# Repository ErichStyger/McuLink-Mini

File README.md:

# McuLink-Mini
Version of the NXP MCU-Link CMSIS-DAP Debug Probe with KiCad.
Many thanks to *Dario Scheuber* and his work to make this project possible!

## Background
This is the work of Dario Scheuber who created this debug probe as student at the Lucerne University of Applied Sciences and Arts at [IET](https://www.hslu.ch/en/lucerne-school-of-engineering-architecture/about-us/organization/institute/engineering-and-technology/elektrotechnik/). The project was done under the guidance of Prof. Erich Styger.

See blog article on https://mcuoneclipse.com/2024/02/06/versatile-oshw-mini-mcu-link-debug-probe-external-on-board-or-embedded/ for additional details.

## Features
This is an open hardware version of the NXP MCU-Link CMSIS-DAP debug probe, with following features and differences to the original MCU-Link:
- Open hardware design with KiCad
- Firmware compatibility with MCU-Link (LinkServer, CMSIS-DAP, ARM DAPLink)
- Dual-Layer design for lower costs
- USB-C connector instead of  Micro-USB
- USB-C connector usable to debug the LPC55S69
- 30% smaller than the original MCU-Link
- Firmware/boot push button instead of jumper
- Micro connector for UART connection instead of pin header
- Supports only 3.3V targets (no level shifters)
- Standalone version as external debug probe
- On-Board version: Solder external debug probe on your custom board (castellated pins)
- Embedded version: copy-paste into your custom board KiCad design
- BOM with assembly costs: ~$12/piece for 100 units

## Folders
- enclosure: 3D printed enclosure
- hardware: KiCad and hardware related files

## Links
- Article: https://mcuoneclipse.com/2024/02/06/versatile-oshw-mini-mcu-link-debug-probe-external-on-board-or-embedded/
- NXP MCU-Link: https://www.nxp.com/design/design-center/software/development-software/mcuxpresso-software-and-tools-/mcu-link-debug-probe:MCU-LINK
- KiCad: https://www.kicad.org/

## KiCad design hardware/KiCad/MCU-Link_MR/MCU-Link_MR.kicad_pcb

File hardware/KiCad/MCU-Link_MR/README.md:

# MCU-Link

Project for the NXP MCU-Link Debug Probe with KiCAD, as a debug drone for mobile robotics platforms.

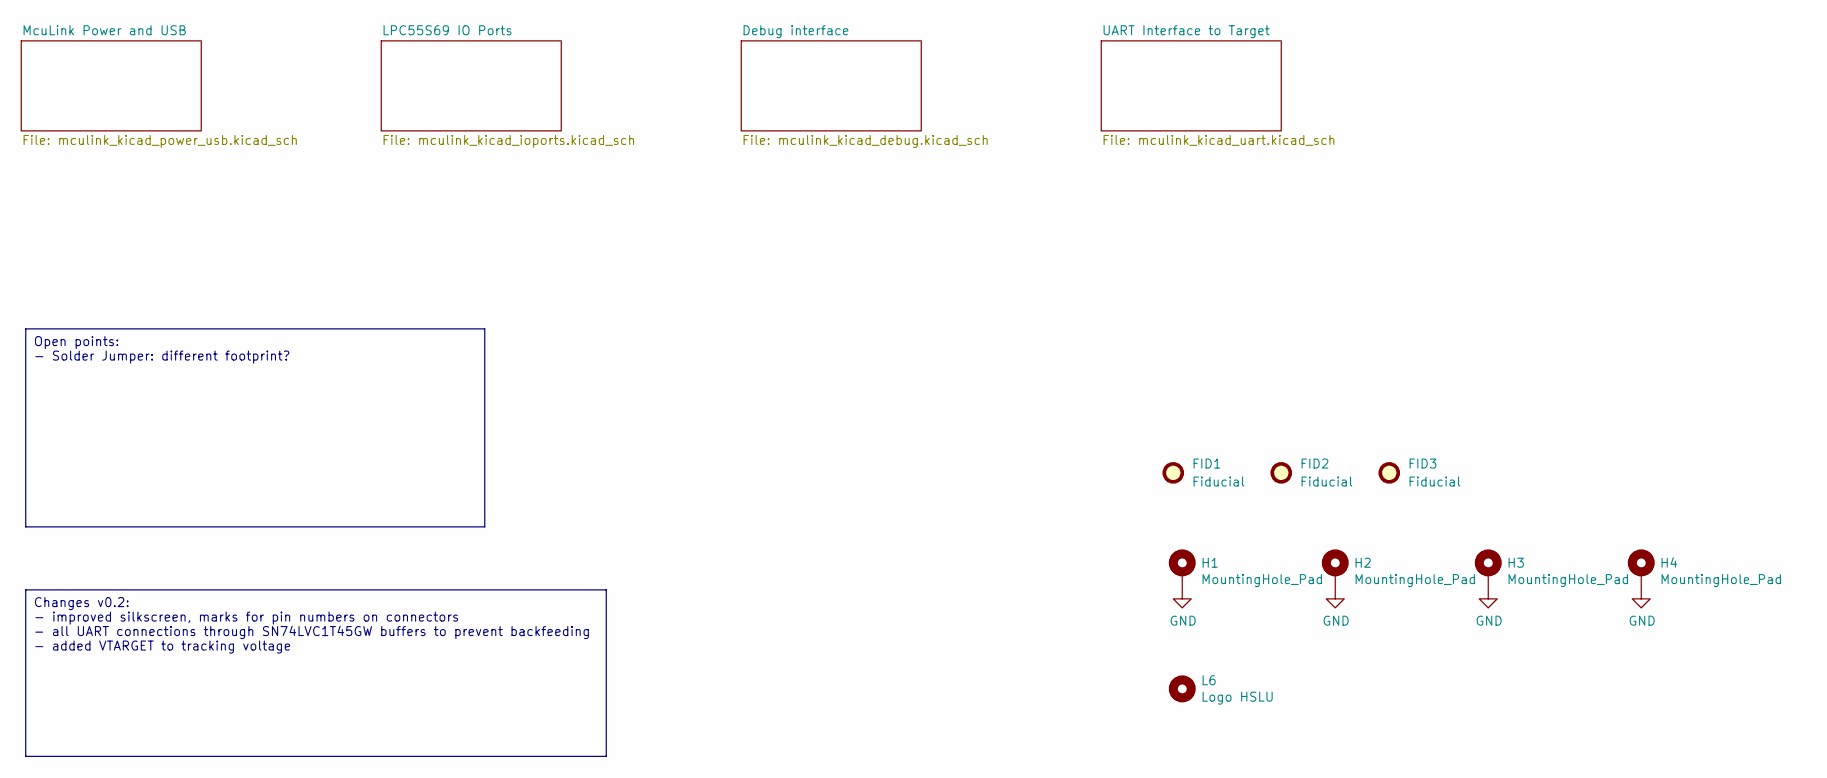
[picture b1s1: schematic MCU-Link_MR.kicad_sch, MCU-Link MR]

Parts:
FID1, FID2, FID3: Fiducial; Fiducial_1mm_Dia_2.54mm_Outer_CopperTop
H1, H2, H3, H4: MountingHole_Pad; MountingHole_2.7mm_M2.5_DIN965_Pad
L6: Logo HSLU; Hochschule_Luzern_New

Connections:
GND: H1.1, H2.1, H3.1, H4.1; also elsewhere on the board

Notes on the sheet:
Open points: - Solder Jumper: different footprint?
Changes v0.2: - improved silkscreen, marks for pin numbers on connectors - all UART connections through SN74LVC1T45GW buffers to prevent backfeeding - added VTARGET to tracking voltage

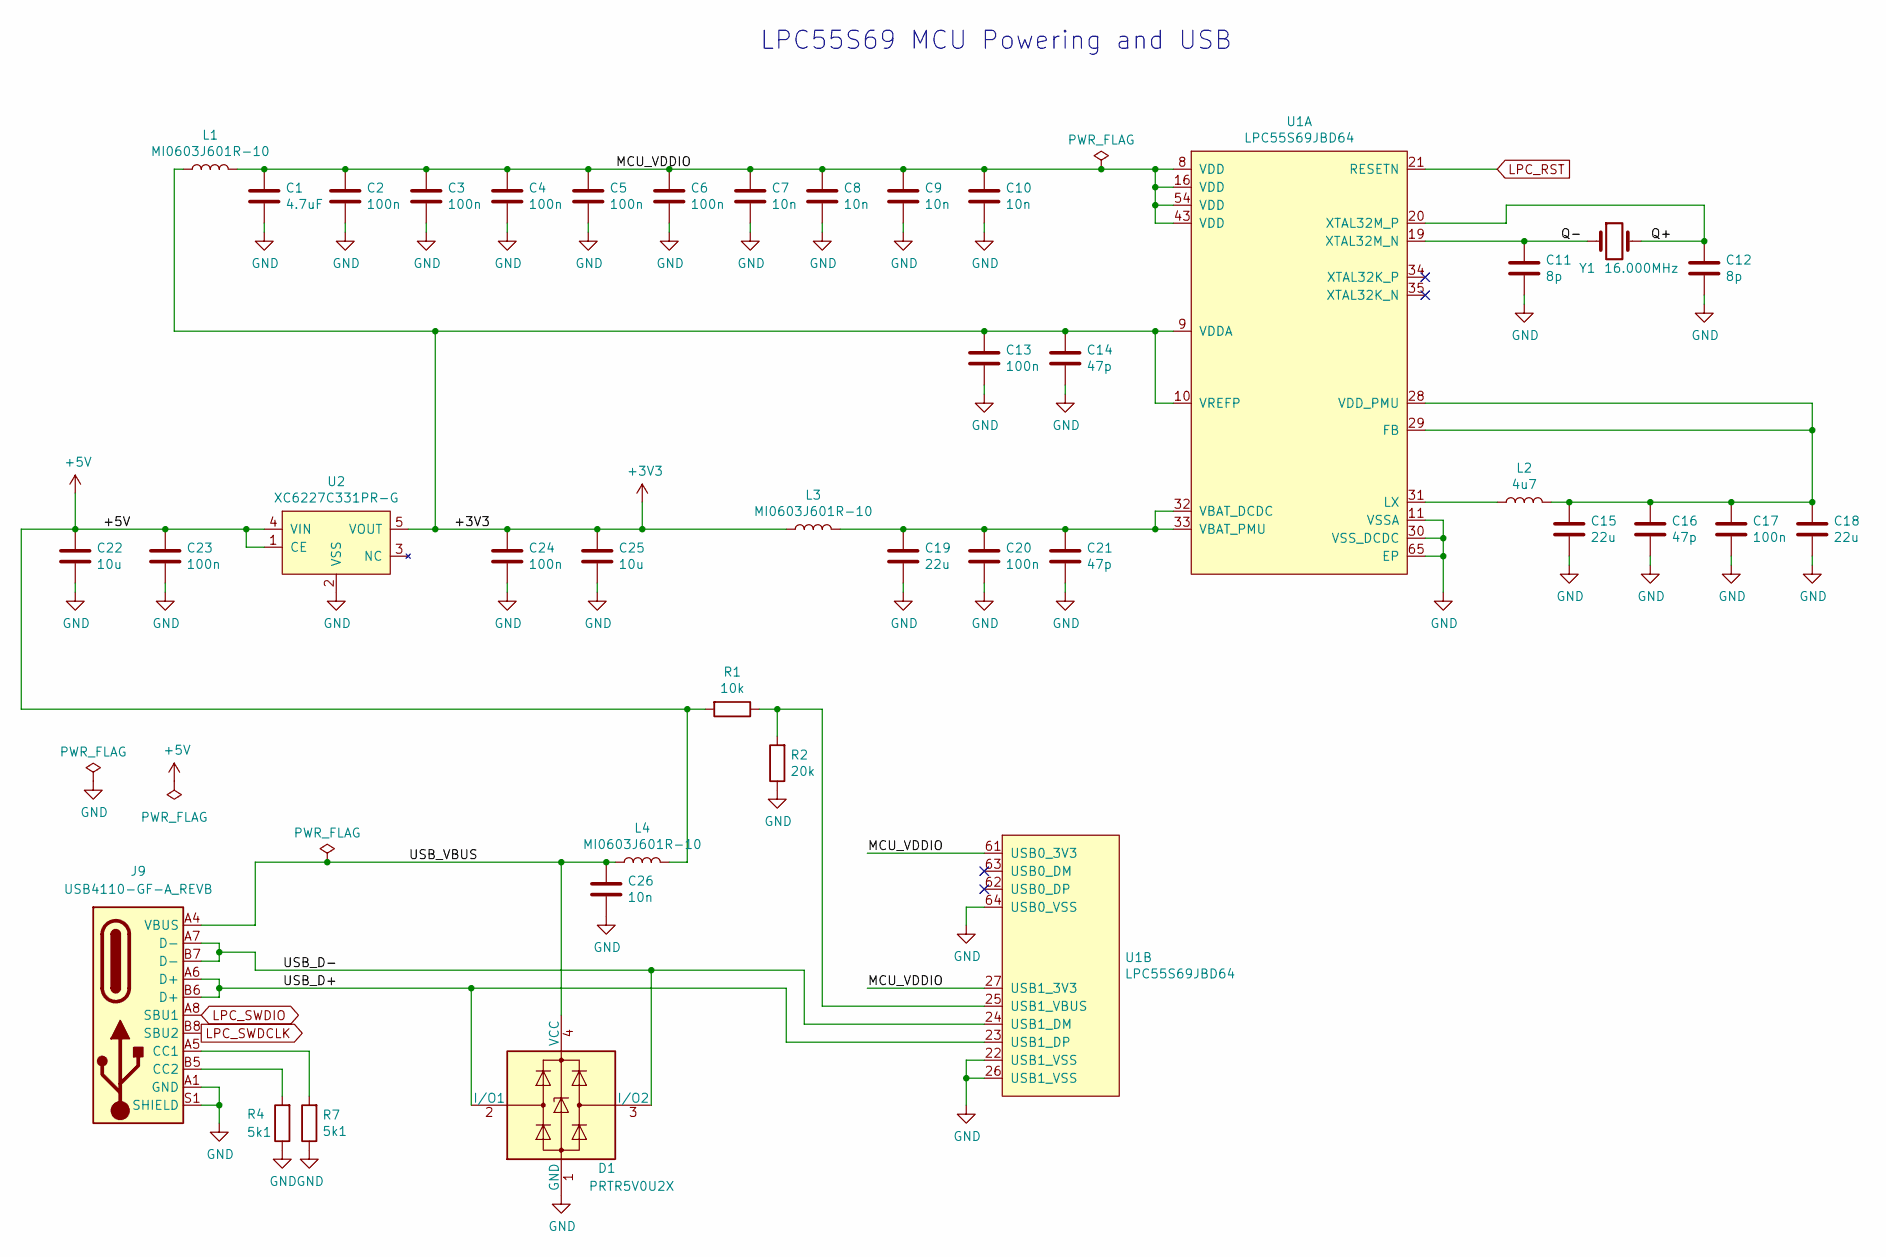
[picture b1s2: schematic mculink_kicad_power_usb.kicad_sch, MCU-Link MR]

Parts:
C1: 4.7uF; C_0603_1608Metric
C2, C3, C4, C5, C6, C13, C17, C20, C23, C24: 100n; C_0603_1608Metric
C7, C8, C9, C10, C26: 10n; C_0603_1608Metric
C11, C12: 8p; C_0603_1608Metric
C14, C16, C21: 47p; C_0603_1608Metric
C15, C19: 22u; C_0805_2012Metric
C18: 22u; C_0603_1608Metric
C22, C25: 10u; C_0603_1608Metric
D1: PRTR5V0U2X; SOT-143
J9: USB4110-GF-A_REVB; USB_C_Receptacle_GCT_USB4110-GF-A; PARTREV B; mouser# 640-USB4110-GF-A
L1, L3, L4: MI0603J601R-10; L_0603_1608Metric
L2: 4u7; L_0805_2012Metric
R1: 10k; R_0603_1608Metric
R2: 20k; R_0603_1608Metric
R4, R7: 5k1; R_0603_1608Metric
U1: LPC55S69JBD64; LQFP-64-1EP_10x10mm_P0.5mm_EP3.5x3.5mm
U2: XC6227C331PR-G; SOT-89-5
Y1: 16.000MHz; CX3225GA16000D0PTVCC

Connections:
+3V3: C13.1, C14.1, C24.1, C25.1, L1.1, L3.1, U1.9 (VDDA), U1.10 (VREFP), U2.5 (VOUT); also elsewhere on the board
+5V: C22.1, C23.1, L4.2, R1.2, U2.1 (CE), U2.4 (VIN); also elsewhere on the board
/McuLink Power and USB/MCU_VDDIO: C1.1, C2.1, C3.1, C4.1, C5.1, C6.1, C7.1, C8.1, C9.1, C10.1, L1.2, U1.8 (VDD), U1.16 (VDD), U1.27 (USB1_3V3), U1.43 (VDD), U1.54 (VDD), U1.61 (USB0_3V3)
/McuLink Power and USB/Q+: C12.1, U1.20 (XTAL32M_P), Y1.2
/McuLink Power and USB/Q-: C11.1, U1.19 (XTAL32M_N), Y1.1
/McuLink Power and USB/USB_D+: D1.2 (I/O1), J9.A6 (D+), J9.B6 (D+), U1.23 (USB1_DP)
/McuLink Power and USB/USB_D-: D1.3 (I/O2), J9.A7 (D-), J9.B7 (D-), U1.24 (USB1_DM)
/McuLink Power and USB/USB_VBUS: C26.1, D1.4 (VCC), J9.A4 (VBUS), J9.A9 (VBUS), J9.B4 (VBUS), J9.B9 (VBUS), L4.1
GND: C1.2, C2.2, C3.2, C4.2, C5.2, C6.2, C7.2, C8.2, C9.2, C10.2, C11.2, C12.2, C13.2, C14.2, C15.2, C16.2, C17.2, C18.2, C19.2, C20.2, C21.2, C22.2, C23.2, C24.2, C25.2, C26.2, D1.1 (GND), J9.A1 (GND), J9.A12 (GND), J9.B1 (GND), J9.B12 (GND), J9.S1 (SHIELD), R2.1, R4.1, R7.1, U1.11 (VSSA), U1.22 (USB1_VSS), U1.26 (USB1_VSS), U1.30 (VSS_DCDC), U1.64 (USB0_VSS), U1.65 (EP), U2.2 (VSS); also elsewhere on the board
LPC_RST: U1.21 (RESETN); also elsewhere on the board
LPC_SWDCLK: J9.B8 (SBU2); also elsewhere on the board
LPC_SWDIO: J9.A8 (SBU1); also elsewhere on the board
unnamed: J9.A5 (CC1), R7.2
unnamed: J9.B5 (CC2), R4.2
unnamed: C15.1, C16.1, C17.1, C18.1, L2.2, U1.28 (VDD_PMU), U1.29 (FB)
unnamed: L2.1, U1.31 (LX)
unnamed: C19.1, C20.1, C21.1, L3.2, U1.32 (VBAT_DCDC), U1.33 (VBAT_PMU)
unnamed: R1.1, R2.2, U1.25 (USB1_VBUS)

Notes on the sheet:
LPC55S69 MCU Powering and USB

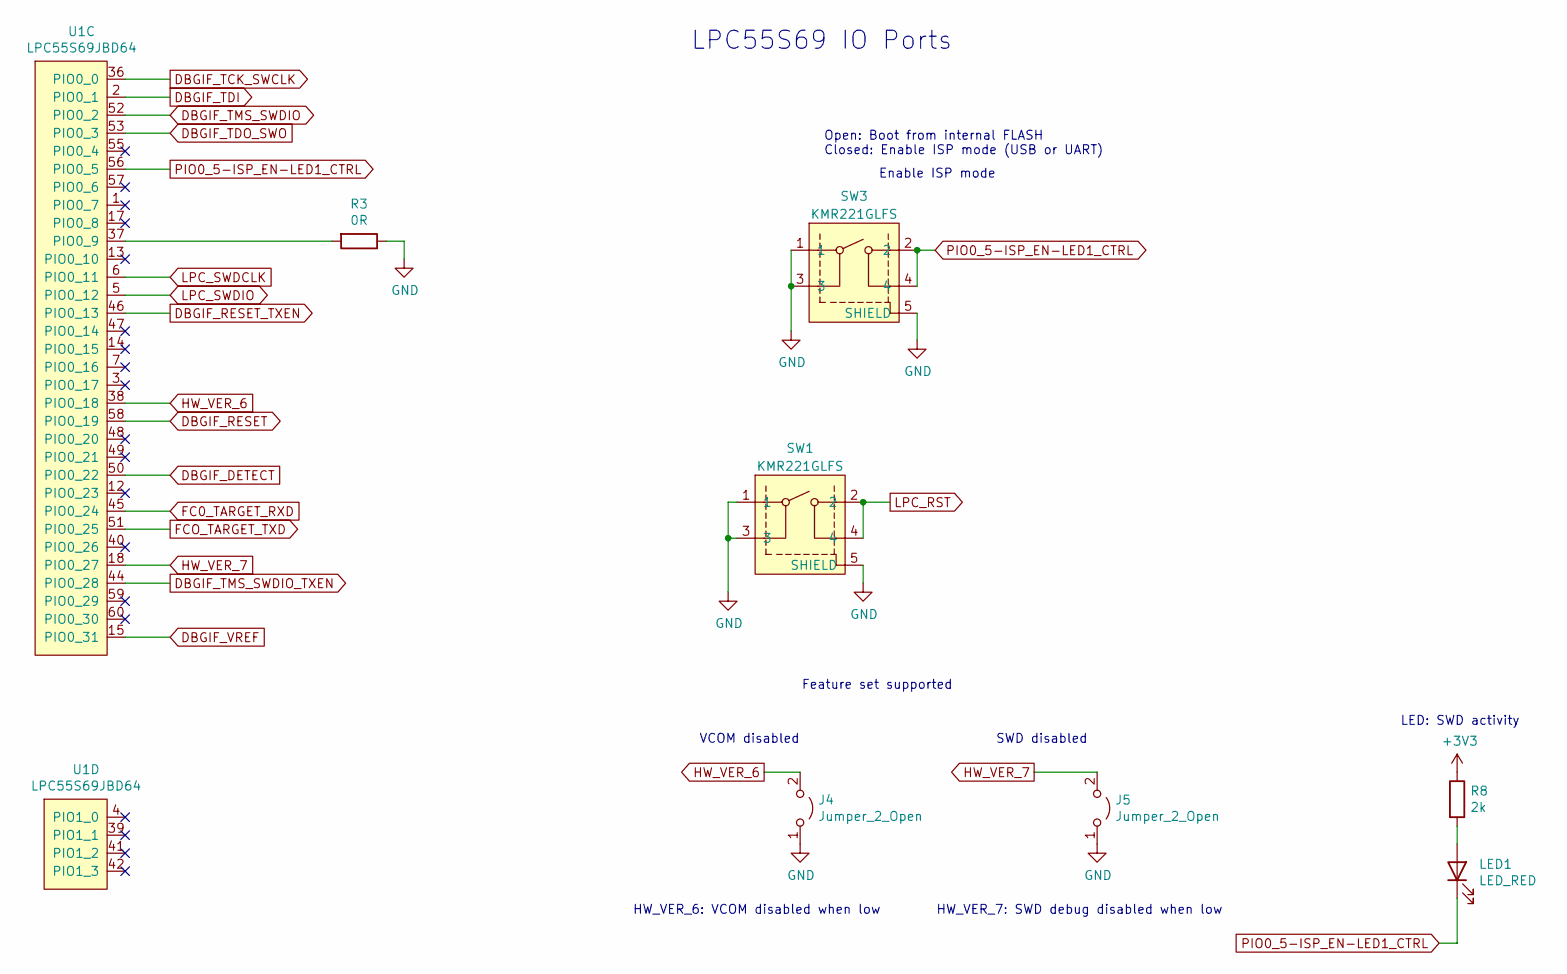
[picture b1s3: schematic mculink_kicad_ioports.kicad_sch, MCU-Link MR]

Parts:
J4, J5: Jumper_2_Open; SolderJumper-2_P1.3mm_Open_RoundedPad1.0x1.5mm
LED1: LED_RED; LED_0603_1608Metric
R3: 0R; R_0603_1608Metric
R8: 2k; R_0603_1608Metric
SW1, SW3: KMR221GLFS; SW_C_K_KMR2
U1: LPC55S69JBD64; LQFP-64-1EP_10x10mm_P0.5mm_EP3.5x3.5mm

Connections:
+3V3: R8.1; also elsewhere on the board
DBGIF_DETECT: U1.50 (PIO0_22); also elsewhere on the board
DBGIF_RESET: U1.58 (PIO0_19); also elsewhere on the board
DBGIF_RESET_TXEN: U1.46 (PIO0_13); also elsewhere on the board
DBGIF_TCK_SWCLK: U1.36 (PIO0_0); also elsewhere on the board
DBGIF_TDI: U1.2 (PIO0_1); also elsewhere on the board
DBGIF_TDO_SWO: U1.53 (PIO0_3); also elsewhere on the board
DBGIF_TMS_SWDIO: U1.52 (PIO0_2); also elsewhere on the board
DBGIF_TMS_SWDIO_TXEN: U1.44 (PIO0_28); also elsewhere on the board
DBGIF_VREF: U1.15 (PIO0_31); also elsewhere on the board
FC0_TARGET_RXD: U1.45 (PIO0_24); also elsewhere on the board
FCO_TARGET_TXD: U1.51 (PIO0_25); also elsewhere on the board
GND: J4.1 (A), J5.1 (A), R3.1, SW1.1, SW1.3, SW1.5 (SHIELD), SW3.1, SW3.3, SW3.5 (SHIELD); also elsewhere on the board
HW_VER_6: J4.2 (B), U1.38 (PIO0_18)
HW_VER_7: J5.2 (B), U1.18 (PIO0_27)
LPC_RST: SW1.2, SW1.4; also elsewhere on the board
LPC_SWDCLK: U1.6 (PIO0_11); also elsewhere on the board
LPC_SWDIO: U1.5 (PIO0_12); also elsewhere on the board
unnamed: LED1.2 (A), R8.2
unnamed: R3.2, U1.37 (PIO0_9)
PIO0_5-ISP_EN-LED1_CTRL: LED1.1 (K), SW3.2, SW3.4, U1.56 (PIO0_5)

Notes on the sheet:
Open: Boot from internal FLASH Closed: Enable ISP mode (USB or UART)
VCOM disabled
Enable ISP mode
HW_VER_7: SWD debug disabled when low
Feature set supported
SWD disabled
LPC55S69 IO Ports
HW_VER_6: VCOM disabled when low
LED: SWD activity

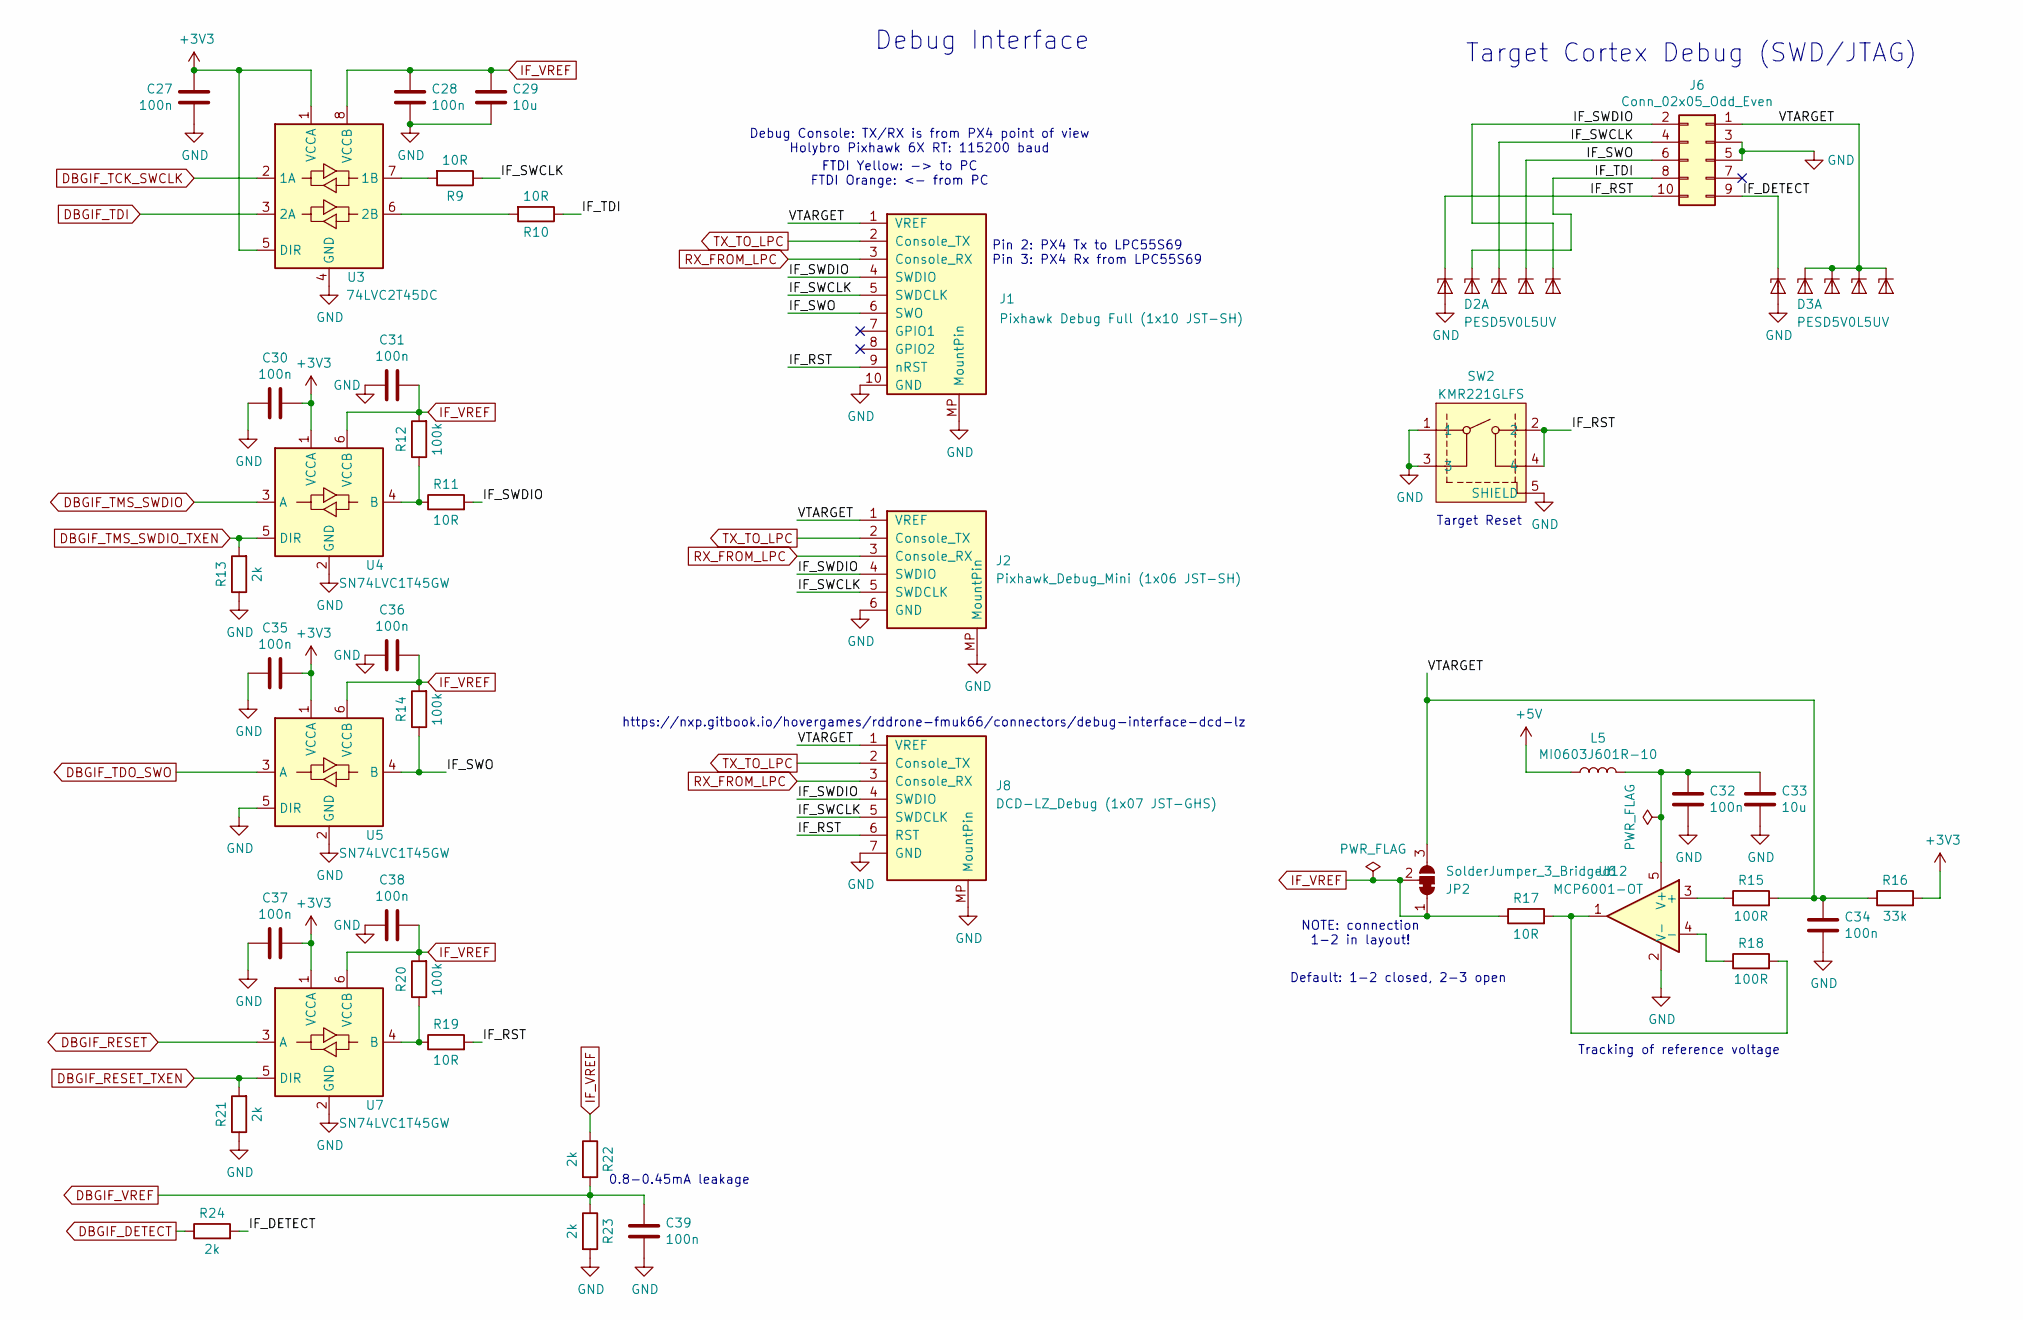
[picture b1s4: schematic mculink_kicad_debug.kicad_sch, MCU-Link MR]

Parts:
C27, C28, C30, C31, C32, C34, C35, C36, C37, C38, C39: 100n; C_0603_1608Metric
C29, C33: 10u; C_0603_1608Metric
D2, D3: PESD5V0L5UV; SOT-666
J1: Pixhawk Debug Full (1x10 JST-SH); JST_SH_SM10B-SRSS-TB_1x10-1MP_P1.00mm_Horizontal
J2: Pixhawk_Debug_Mini (1x06 JST-SH); JST_SH_BM06B-SRSS-TB_1x06-1MP_P1.00mm_Vertical
J6: Conn_02x05_Odd_Even; SWD_Pin_Header_Straight_2x05_Pitch1.27mm_SMD_Shrouded
J8: DCD-LZ_Debug (1x07 JST-GHS); JST_GH_SM07B-GHS-TB_1x07-1MP_P1.25mm_Horizontal
JP2: SolderJumper_3_Bridged12; SolderJumper-3_P1.3mm_Open_RoundedPad1.0x1.5mm
L5: MI0603J601R-10; L_0603_1608Metric
R9, R10, R11, R17, R19: 10R; R_0603_1608Metric
R12, R14, R20: 100k; R_0603_1608Metric
R13, R21, R22, R23, R24: 2k; R_0603_1608Metric
R15, R18: 100R; R_0603_1608Metric
R16: 33k; R_0603_1608Metric
SW2: KMR221GLFS; SW_C_K_KMR2
U3: 74LVC2T45DC; VSSOP-8_2.3x2mm_P0.5mm
U4, U5, U7: SN74LVC1T45GW; SOT-363_SC-70-6
U6: MCP6001-OT; SOT-23-5

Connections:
+3V3: C27.2, C30.2, C35.2, C37.2, R16.2, U3.1 (VCCA), U3.5 (DIR), U4.1 (VCCA), U5.1 (VCCA), U7.1 (VCCA); also elsewhere on the board
+5V: L5.1; also elsewhere on the board
/Debug interface/IF_DETECT: D3.1 (K1), J6.9, R24.2
/Debug interface/IF_RST: D2.1 (K1), J1.9 (nRST), J6.10, J8.6 (RST), R19.2, SW2.2, SW2.4
/Debug interface/IF_SWCLK: D2.4 (K3), J1.5 (SWDCLK), J2.5 (SWDCLK), J6.4, J8.5 (SWDCLK), R9.1
/Debug interface/IF_SWDIO: D2.6 (K5), J1.4 (SWDIO), J2.4 (SWDIO), J6.2, J8.4 (SWDIO), R11.2
/Debug interface/IF_SWO: D2.5 (K4), J1.6 (SWO), J6.6, R14.1, U5.4 (B)
/Debug interface/IF_TDI: D2.3 (K2), J6.8, R10.1
/Debug interface/VTARGET: C34.1, D3.3 (K2), D3.4 (K3), D3.5 (K4), D3.6 (K5), J1.1 (VREF), J2.1 (VREF), J6.1, J8.1 (VREF), JP2.3 (B), R15.2, R16.1
DBGIF_DETECT: R24.1; also elsewhere on the board
DBGIF_RESET: U7.3 (A); also elsewhere on the board
DBGIF_RESET_TXEN: R21.2, U7.5 (DIR); also elsewhere on the board
DBGIF_TCK_SWCLK: U3.2 (1A); also elsewhere on the board
DBGIF_TDI: U3.3 (2A); also elsewhere on the board
DBGIF_TDO_SWO: U5.3 (A); also elsewhere on the board
DBGIF_TMS_SWDIO: U4.3 (A); also elsewhere on the board
DBGIF_TMS_SWDIO_TXEN: R13.2, U4.5 (DIR); also elsewhere on the board
DBGIF_VREF: C39.1, R22.2, R23.1; also elsewhere on the board
GND: C27.1, C28.2, C29.2, C30.1, C31.1, C32.2, C33.2, C34.2, C35.1, C36.1, C37.1, C38.1, C39.2, D2.2 (A), D3.2 (A), J1.10 (GND), J1.MP (MountPin), J2.6 (GND), J2.MP (MountPin), J6.3, J6.5, J8.7 (GND), J8.MP (MountPin), R13.1, R21.1, R23.2, SW2.1, SW2.3, SW2.5 (SHIELD), U3.4 (GND), U4.2 (GND), U5.2 (GND), U5.5 (DIR), U6.2 (V-), U7.2 (GND); also elsewhere on the board
IF_VREF: C28.1, C29.1, C31.2, C36.2, C38.2, JP2.1 (A), JP2.2 (C), R12.2, R14.2, R17.1, R20.2, R22.1, U3.8 (VCCB), U4.6 (VCCB), U5.6 (VCCB), U7.6 (VCCB); also elsewhere on the board
unnamed: R17.2, R18.2, U6.1
unnamed: R9.2, U3.7 (1B)
unnamed: R10.2, U3.6 (2B)
unnamed: R11.1, R12.1, U4.4 (B)
unnamed: R15.1, U6.3 (+)
unnamed: R18.1, U6.4 (-)
unnamed: C32.1, C33.1, L5.2, U6.5 (V+)
unnamed: R19.1, R20.1, U7.4 (B)
RX_FROM_LPC: J1.3 (Console_RX), J2.3 (Console_RX), J8.3 (Console_RX); also elsewhere on the board
TX_TO_LPC: J1.2 (Console_TX), J2.2 (Console_TX), J8.2 (Console_TX); also elsewhere on the board

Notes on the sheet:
NOTE: connection 1-2 in layout!
Tracking of reference voltage
Target Cortex Debug (SWD/JTAG)
Target Reset
https://nxp.gitbook.io/hovergames/rddrone-fmuk66/connectors/debug-interface-dcd-lz
FTDI Yellow: -> to PC FTDI Orange: <- from PC
Debug Console: TX/RX is from PX4 point of view Holybro Pixhawk 6X RT: 115200 baud
0.8-0.45mA leakage
Pin 2: PX4 Tx to LPC55S69 Pin 3: PX4 Rx from LPC55S69
Debug Interface
Default: 1-2 closed, 2-3 open

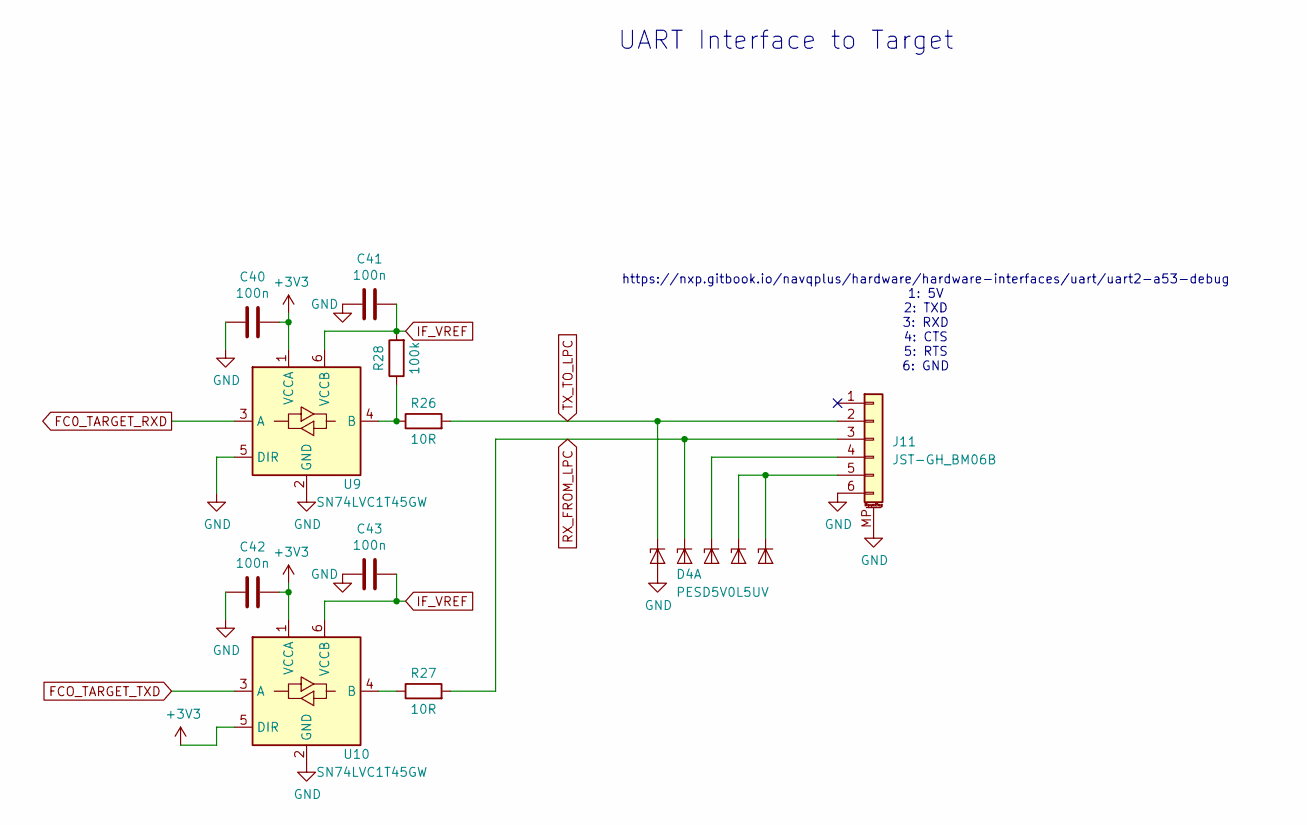
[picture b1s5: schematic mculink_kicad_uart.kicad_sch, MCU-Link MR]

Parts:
C40, C41, C42, C43: 100n; C_0603_1608Metric
D4: PESD5V0L5UV; SOT-666
J11: JST-GH_BM06B; JST_GH_BM06B-GHS-TBT_1x06-1MP_P1.25mm_Vertical
R26, R27: 10R; R_0603_1608Metric
R28: 100k; R_0603_1608Metric
U9, U10: SN74LVC1T45GW; SOT-363_SC-70-6

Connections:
+3V3: C40.2, C42.2, U9.1 (VCCA), U10.1 (VCCA), U10.5 (DIR); also elsewhere on the board
FC0_TARGET_RXD: U9.3 (A); also elsewhere on the board
FCO_TARGET_TXD: U10.3 (A); also elsewhere on the board
GND: C40.1, C41.1, C42.1, C43.1, D4.2 (A), J11.6, J11.MP (MountPin), U9.2 (GND), U9.5 (DIR), U10.2 (GND); also elsewhere on the board
IF_VREF: C41.2, C43.2, R28.2, U9.6 (VCCB), U10.6 (VCCB); also elsewhere on the board
unnamed: D4.4 (K3), J11.4
unnamed: D4.5 (K4), D4.6 (K5), J11.5
unnamed: R26.1, R28.1, U9.4 (B)
unnamed: R27.1, U10.4 (B)
RX_FROM_LPC: D4.3 (K2), J11.3, R27.2; also elsewhere on the board
TX_TO_LPC: D4.1 (K1), J11.2, R26.2; also elsewhere on the board

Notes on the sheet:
UART Interface to Target
https://nxp.gitbook.io/navqplus/hardware/hardware-interfaces/uart/uart2-a53-debug 1: 5V 2: TXD 3: RXD 4: CTS 5: RTS 6: GND

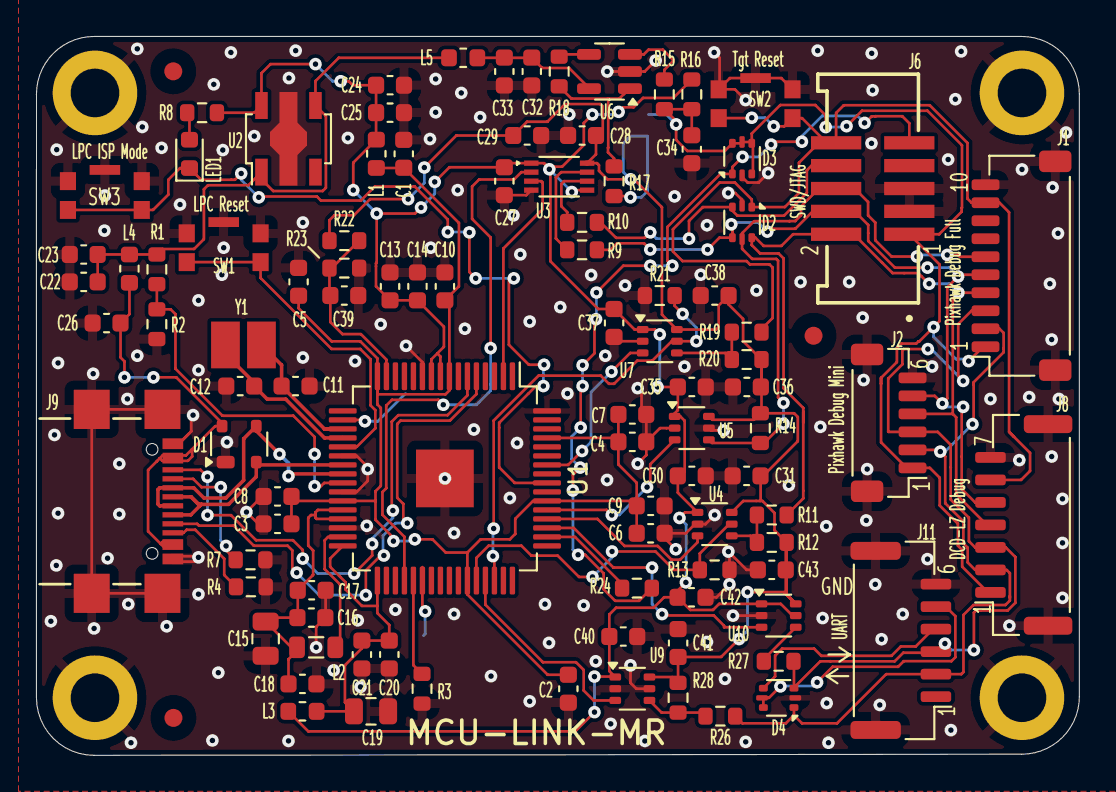
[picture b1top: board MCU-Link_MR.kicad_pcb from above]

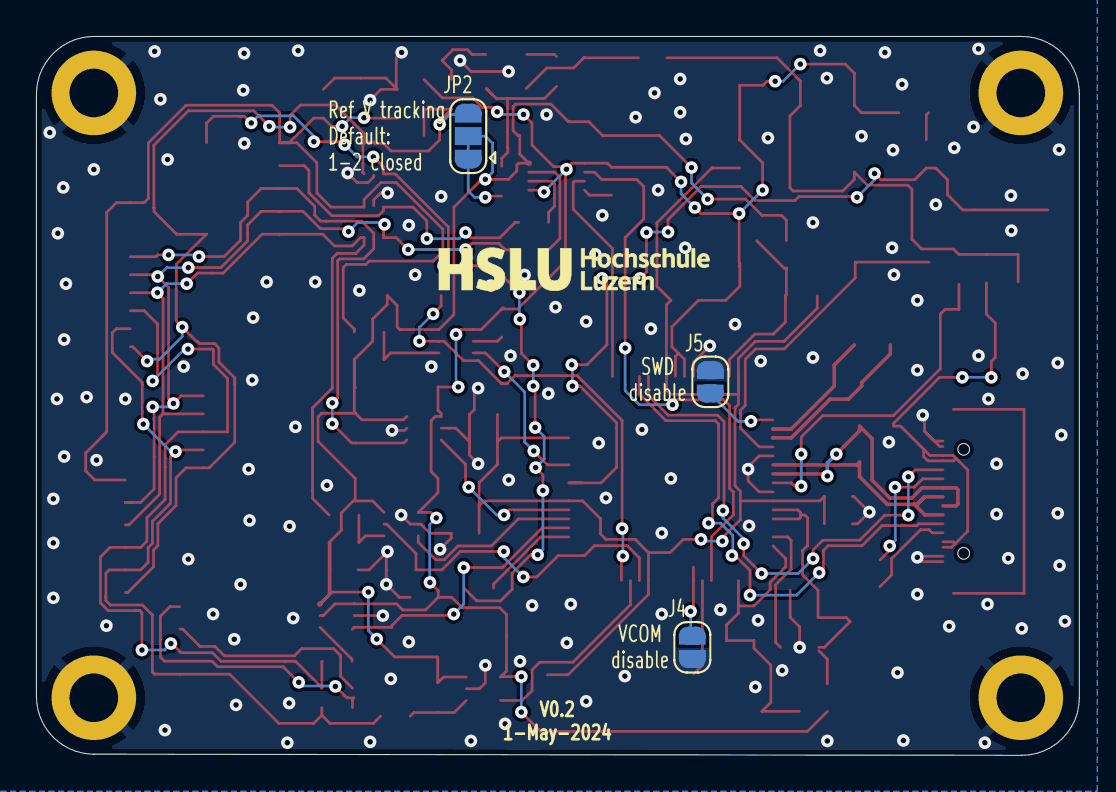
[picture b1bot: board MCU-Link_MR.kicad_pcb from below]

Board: 2 copper layers, 57.9 x 39.9 mm, 108 parts (4 on the bottom side), 56 nets.

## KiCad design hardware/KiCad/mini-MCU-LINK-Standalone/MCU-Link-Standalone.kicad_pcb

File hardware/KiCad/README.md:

Different versions of the debug probe:
- Standalone: used as standalone external debug probe
- Integrated: schematic and layout which can be pasted in your custom design
- Component: to place the standalone version with the castellated pins as component on your board

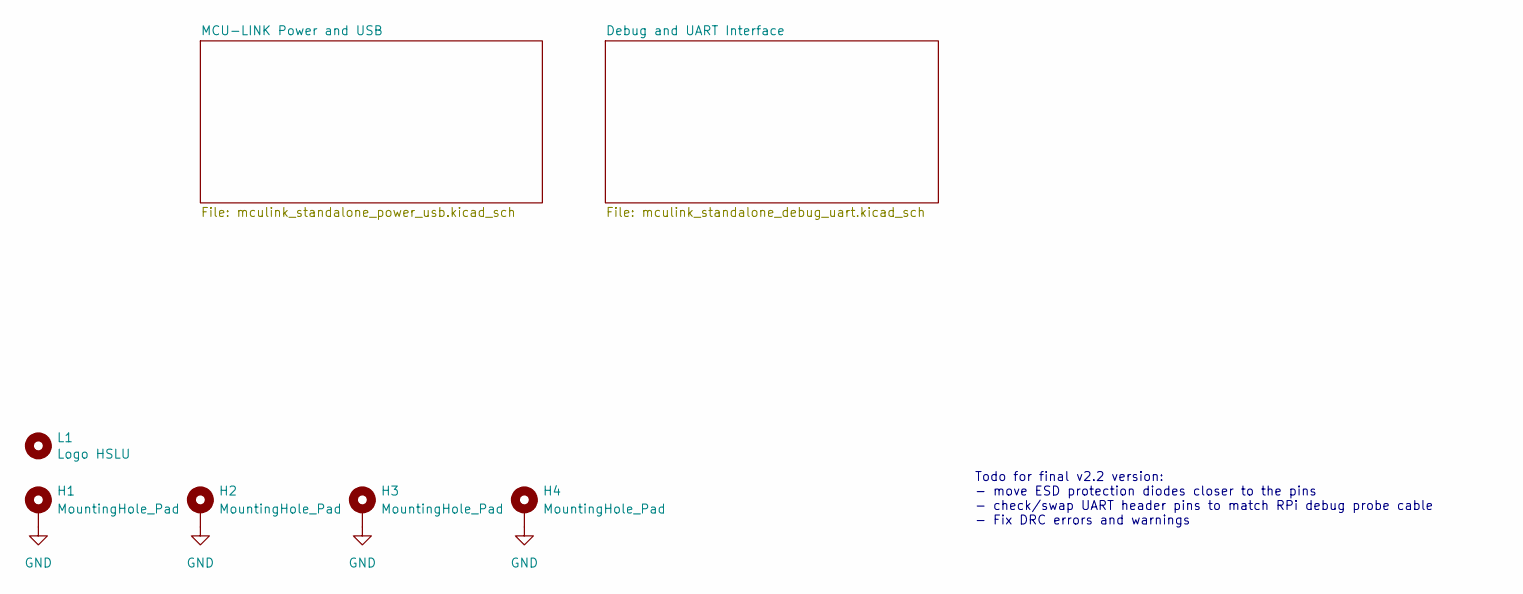
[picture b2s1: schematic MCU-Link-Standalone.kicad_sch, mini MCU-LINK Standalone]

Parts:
H1, H2, H3, H4: MountingHole_Pad; MountingHole_2.2mm_M2_ISO7380_Pad_TopBottom_with_holes
L1: Logo HSLU; Hochschule_Luzern_New

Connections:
GND: H1.1, H2.1, H3.1, H4.1; also elsewhere on the board

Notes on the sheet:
Todo for final v2.2 version: - move ESD protection diodes closer to the pins - check/swap UART header pins to match RPi debug probe cable - Fix DRC errors and warnings

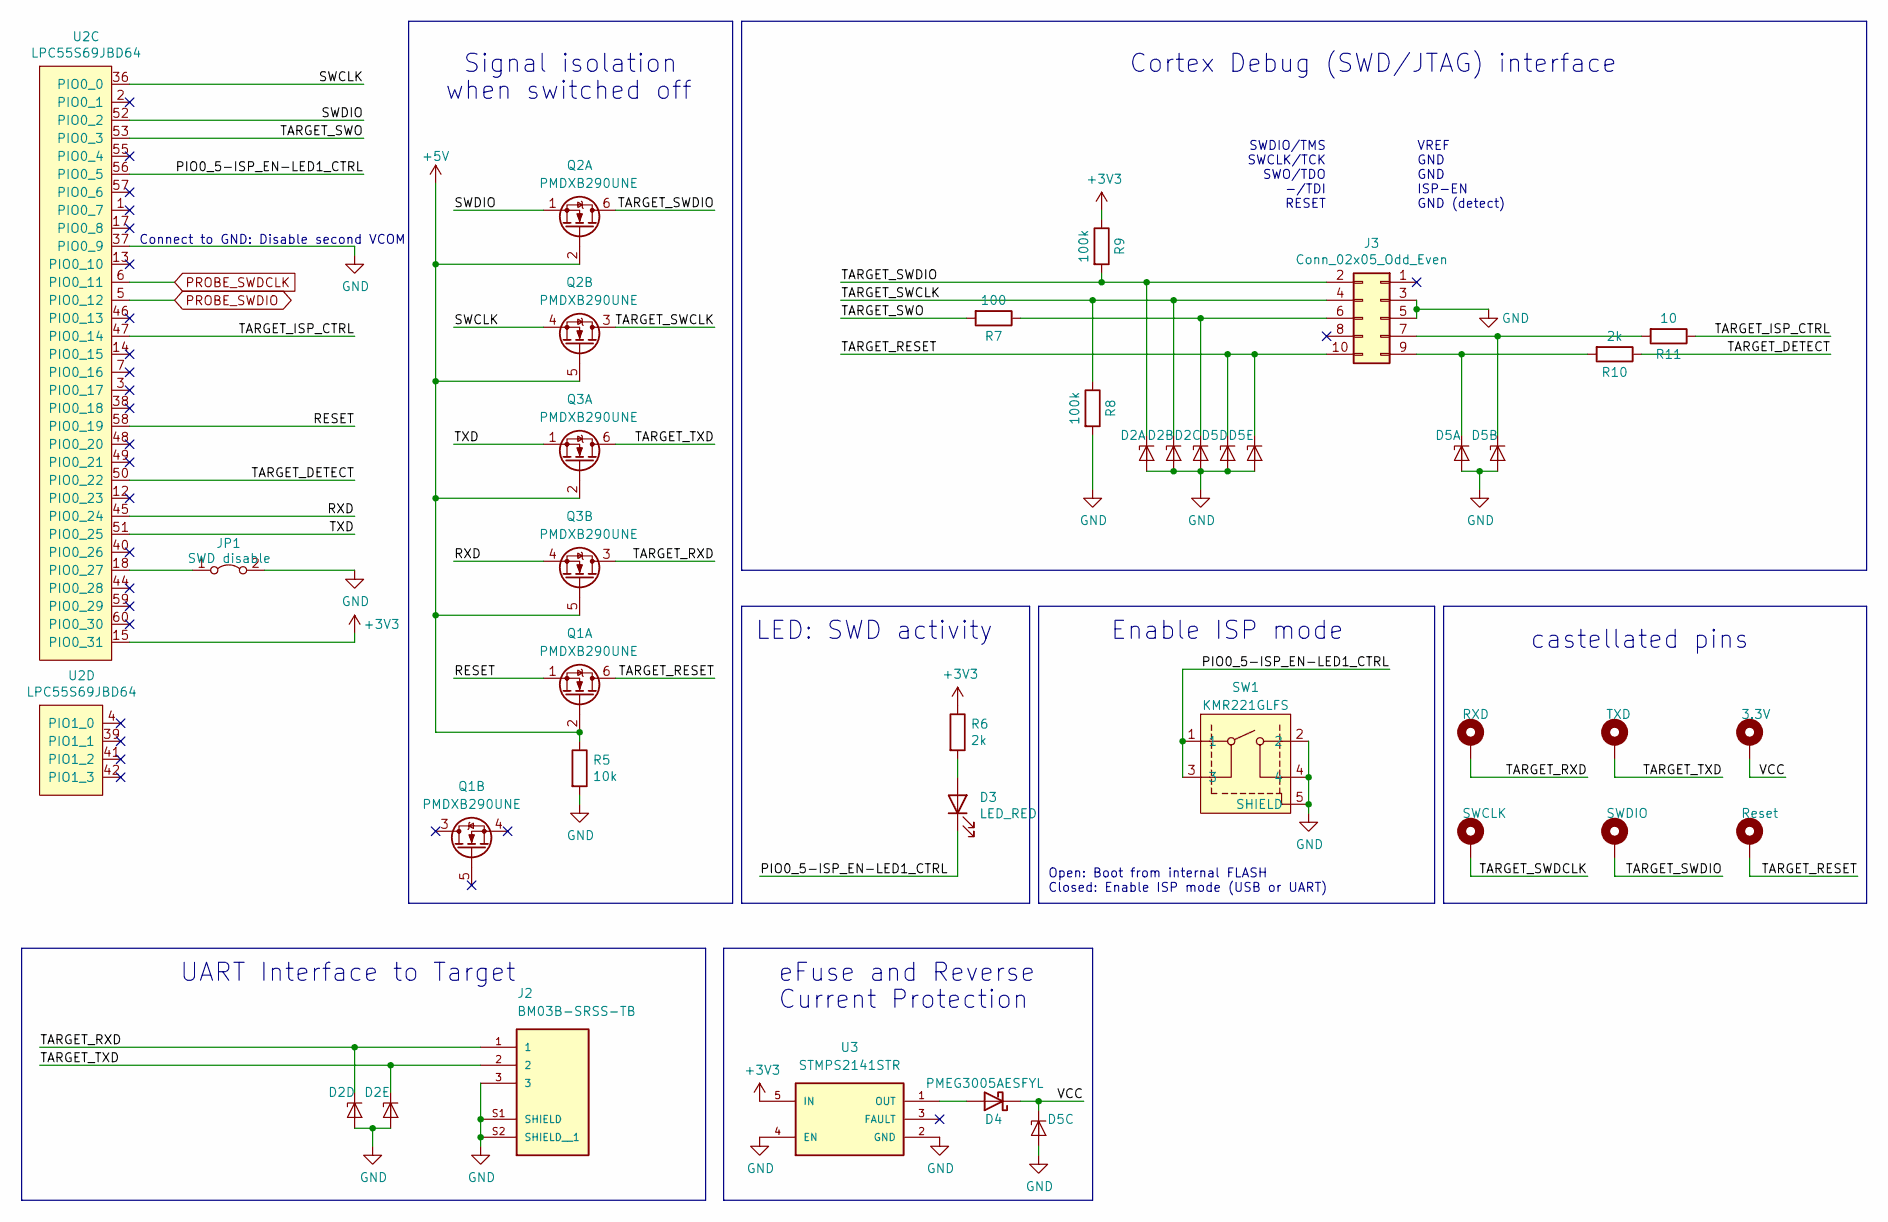
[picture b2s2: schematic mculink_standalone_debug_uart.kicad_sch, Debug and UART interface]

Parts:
D2, D5: PESD5V0L5UV; SOT-666
D3: LED_RED; LED_0402_1005Metric
D4: PMEG3005AESFYL; Nexperia_DSN0603-2_0.6x0.3mm_P0.4mm
H5: RXD; castellated pin
H6: SWCLK; castellated pin
H7: TXD; castellated pin
H8: SWDIO; castellated pin
H9: 3.3V; castellated pin
H10: Reset; castellated pin
J2: BM03B-SRSS-TB; JST_BM03B-SRSS-TB_LF__SN_; PARTREV N/A
J3: Conn_02x05_Odd_Even; SWD_Pin_Header_Straight_2x05_Pitch1.27mm_SMD
JP1: SWD disable; SolderJumper-2_P1.3mm_Open_RoundedPad1.0x1.5mm
Q1, Q2, Q3: PMDXB290UNE; SOT1216
R5: 10k; R_0402_1005Metric
R6, R10: 2k; R_0402_1005Metric
R7: 100; R_0402_1005Metric
R8, R9: 100k; R_0402_1005Metric
R11: 10; R_0402_1005Metric
SW1: KMR221GLFS; SW_C_K_KMR2
U2: LPC55S69JBD64; LQFP-64-1EP_10x10mm_P0.5mm_EP5x5mm
U3: STMPS2141STR; SOT95P280X145-5N

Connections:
+3V3: R6.1, R9.1, U2.15 (PIO0_31), U3.5 (IN); also elsewhere on the board
+5V: Q1.2 (G), Q2.2 (G), Q2.5 (G), Q3.2 (G), Q3.5 (G), R5.1; also elsewhere on the board
/Debug and UART Interface/PIO0_5-ISP_EN-LED1_CTRL: D3.1 (K), SW1.1, SW1.3, U2.56 (PIO0_5)
/Debug and UART Interface/RESET: Q1.1 (S), U2.58 (PIO0_19)
/Debug and UART Interface/RXD: Q3.4 (S), U2.45 (PIO0_24)
/Debug and UART Interface/SWCLK: Q2.4 (S), U2.36 (PIO0_0)
/Debug and UART Interface/SWDIO: Q2.1 (S), U2.52 (PIO0_2)
/Debug and UART Interface/TARGET_DETECT: R10.1, U2.50 (PIO0_22)
/Debug and UART Interface/TARGET_ISP_CTRL: R11.1, U2.47 (PIO0_14)
/Debug and UART Interface/TARGET_RESET: D5.5 (K4), D5.6 (K5), H10.1, J3.10, Q1.6 (D)
/Debug and UART Interface/TARGET_RXD: D2.5 (K4), H5.1, J2.1, Q3.3 (D)
/Debug and UART Interface/TARGET_SWCLK: D2.3 (K2), J3.4, Q2.3 (D), R8.1
/Debug and UART Interface/TARGET_SWDCLK: H6.1
/Debug and UART Interface/TARGET_SWDIO: D2.1 (K1), H8.1, J3.2, Q2.6 (D), R9.2
/Debug and UART Interface/TARGET_SWO: R7.2, U2.53 (PIO0_3)
/Debug and UART Interface/TARGET_TXD: D2.6 (K5), H7.1, J2.2, Q3.6 (D)
/Debug and UART Interface/TXD: Q3.1 (S), U2.51 (PIO0_25)
/Debug and UART Interface/VCC: D4.1 (K), D5.4 (K3), H9.1
GND: D2.2 (A), D5.2 (A), J2.3, J2.S1 (SHIELD), J2.S2 (SHIELD__1), J3.3, J3.5, JP1.2 (B), R5.2, R8.2, SW1.2, SW1.4, SW1.5 (SHIELD), U2.37 (PIO0_9), U3.2 (GND), U3.4 (EN); also elsewhere on the board
unnamed: D2.4 (K3), J3.6, R7.1
unnamed: D3.2 (A), R6.2
unnamed: D4.2 (A), U3.1 (OUT)
unnamed: D5.1 (K1), J3.9, R10.2
unnamed: D5.3 (K2), J3.7, R11.2
unnamed: JP1.1 (A), U2.18 (PIO0_27)
PROBE_SWDCLK: U2.6 (PIO0_11); also elsewhere on the board
PROBE_SWDIO: U2.5 (PIO0_12); also elsewhere on the board

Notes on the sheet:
Connect to GND: Disable second VCOM
when switched off
VREF GND GND ISP-EN GND (detect)
UART Interface to Target
SWDIO/TMS SWCLK/TCK SWO/TDO -/TDI RESET
Cortex Debug (SWD/JTAG) interface
LED: SWD activity
eFuse and Reverse
Signal isolation
castellated pins
Enable ISP mode
Current Protection
Open: Boot from internal FLASH Closed: Enable ISP mode (USB or UART)
